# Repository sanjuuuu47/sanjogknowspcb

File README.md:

# Description:
A key held by the Owl's. It shines at it's full potential only when the sun is raging, only then will it be able to fullfill it's role of being the artifact held by the Owl's.
# Parts list:
Battery x1 Push Switch x1 Photoresistor x1 Resistor x6 LED x3
# Some Glimpses

# slack id; sanjogpandey47

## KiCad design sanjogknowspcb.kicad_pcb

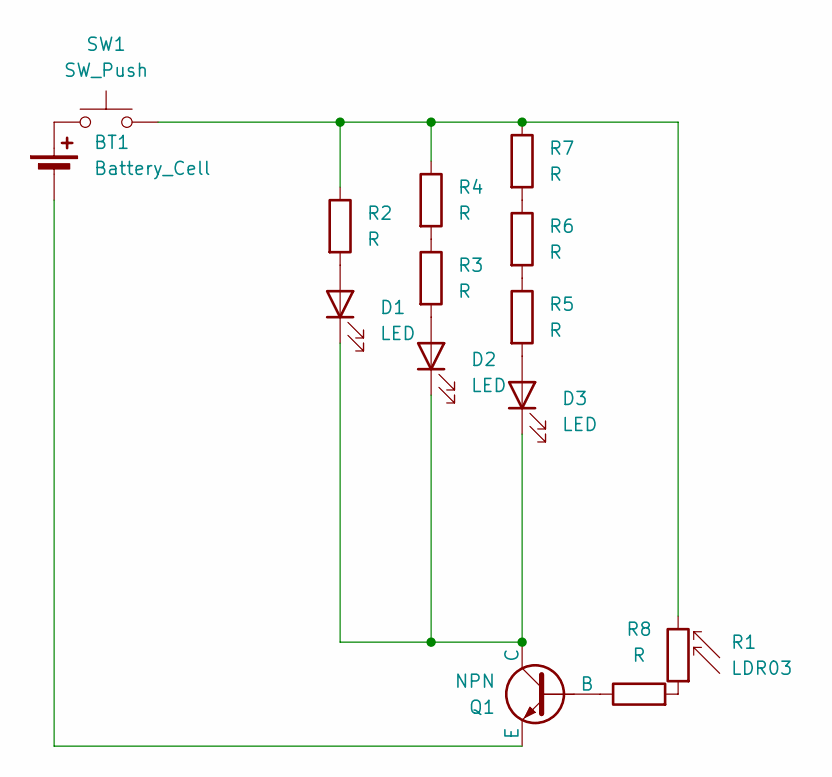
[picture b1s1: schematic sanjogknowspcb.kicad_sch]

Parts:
BT1: Battery_Cell; BatteryHolder_Keystone_3034_1x20mm
D1, D2, D3: LED; LED_D5.0mm
Q1: NPN; TO-92L_HandSolder
R1: LDR03; R_LDR_5.1x4.3mm_P3.4mm_Vertical
R2, R3, R4, R5, R6, R7, R8: R; R_Axial_DIN0207_L6.3mm_D2.5mm_P7.62mm_Horizontal
SW1: SW_Push; SW_PUSH_6mm

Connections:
unnamed: BT1.1 (+), SW1.1
unnamed: BT1.2 (-), Q1.3 (E)
unnamed: D1.2 (A), R2.2
unnamed: D1.1 (K), D2.1 (K), D3.1 (K), Q1.1 (C)
unnamed: D2.2 (A), R3.2
unnamed: D3.2 (A), R5.2
unnamed: Q1.2 (B), R8.1
unnamed: R1.1, R8.2
unnamed: R1.2, R2.1, R4.1, R7.1, SW1.2
unnamed: R3.1, R4.2
unnamed: R5.1, R6.2
unnamed: R6.1, R7.2

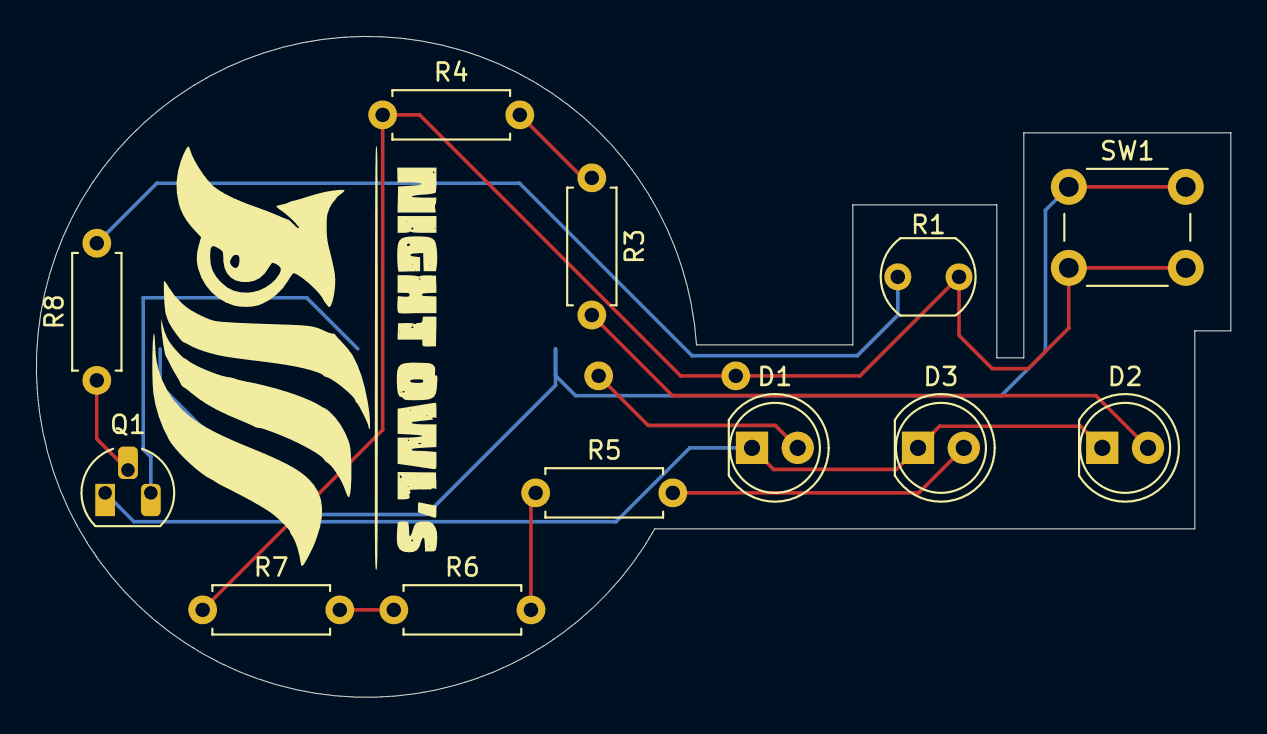
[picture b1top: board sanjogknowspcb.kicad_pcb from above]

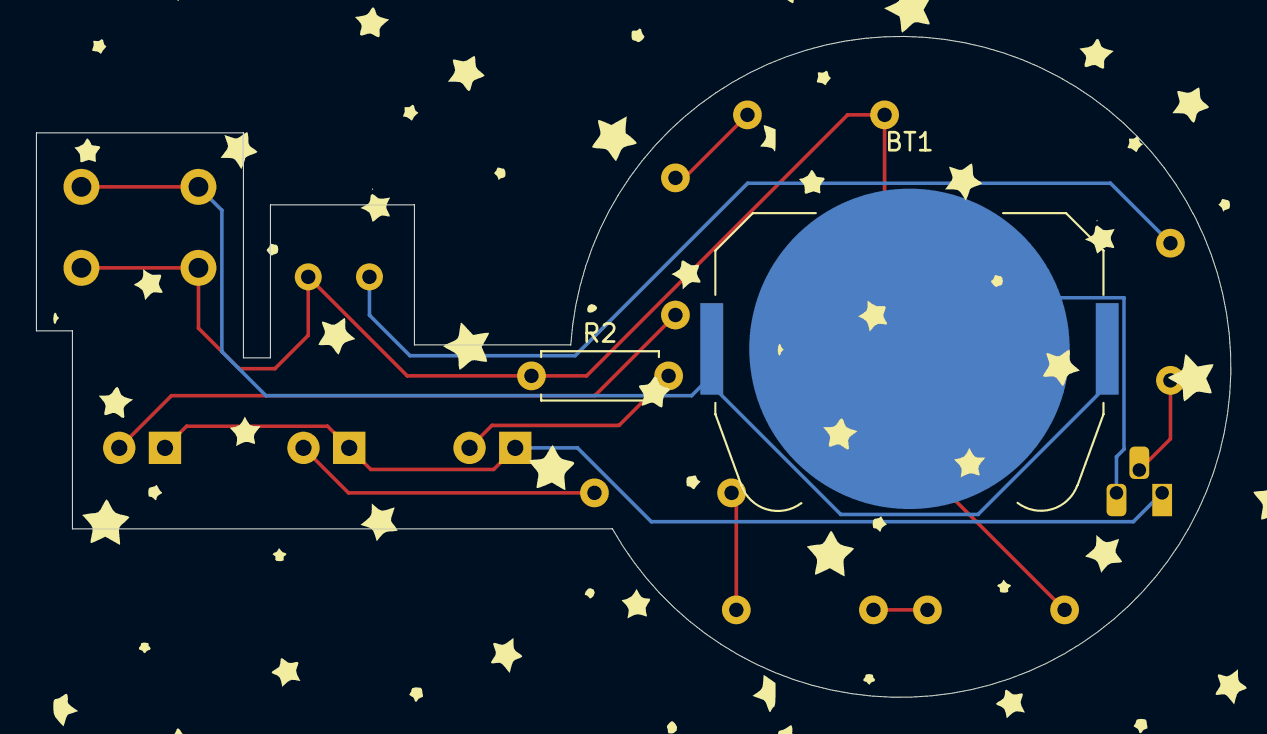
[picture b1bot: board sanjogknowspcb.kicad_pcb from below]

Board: 2 copper layers, 66.4 x 36.7 mm, 14 parts (2 on the bottom side), 12 nets.

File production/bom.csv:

Designator,Footprint,Quantity,Value,LCSC Part #
BT1,BatteryHolder_Keystone_3034_1x20mm,1,Battery_Cell,
"D1, D2, D3",LED_D5.0mm,3,LED,
Q1,TO-92L_HandSolder,1,NPN,
R1,R_LDR_5.1x4.3mm_P3.4mm_Vertical,1,LDR03,
"R2, R3, R4, R5, R6, R7, R8",R_Axial_DIN0207_L6.3mm_D2.5mm_P7.62mm_Horizontal,7,R,
SW1,SW_PUSH_6mm,1,SW_Push,
